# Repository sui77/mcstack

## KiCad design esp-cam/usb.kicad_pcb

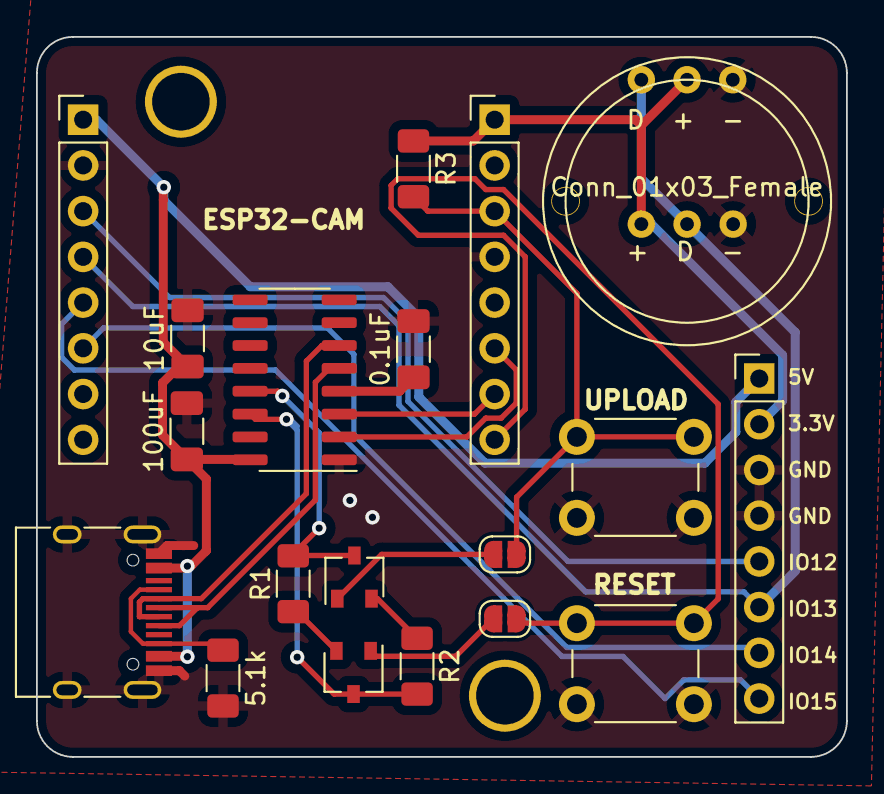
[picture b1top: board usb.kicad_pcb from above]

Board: 2 copper layers, 45.0 x 40.0 mm, 19 parts (0 on the bottom side), 21 nets.

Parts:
C1: 0.1uF; C_1206_3216Metric_Pad1.33x1.80mm_HandSolder
C3: 100uF; C_1206_3216Metric_Pad1.33x1.80mm_HandSolder
C4: 10uF; C_1206_3216Metric_Pad1.33x1.80mm_HandSolder
J1, J2, J5: Conn_01x08_Female; PinHeader_1x08_P2.54mm_Vertical
J3: USB_C_Receptacle; USB_C_Receptacle_HRO_TYPE-C-31-M-12
J4: Conn_01x03_Female; PIR
JP1, JP2: SolderJumper_2_Open; SolderJumper-2_P1.3mm_Open_RoundedPad1.0x1.5mm
Q1, Q2: BC547; SOT-23W
R1, R2, R3: R; R_1206_3216Metric_Pad1.30x1.75mm_HandSolder
R4: 5.1k; R_1206_3216Metric_Pad1.30x1.75mm_HandSolder
SW1, SW2: SW_Push; SW_PUSH_6mm
U1: CH340G; SOIC-16_3.9x9.9mm_P1.27mm

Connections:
3.3V: J2.1, J4.2, J5.2, R3.1
D+: J3.A6 (D+), J3.B6 (D+), U1.5 (UD+)
D-: J3.A7 (D-), J3.B7 (D-), U1.6 (UD-)
GND: C1.1, C3.1, C4.1, J1.2, J2.4, J3.A1 (GND), J3.A12 (GND), J3.B1 (GND), J3.B12 (GND), J3.S1 (SHIELD), J4.3, J5.3, J5.4, R4.1, SW1.2, SW2.2, U1.1 (GND)
GPIO0: J2.3, JP2.2 (B), R3.2, SW1.1
GPIO12: J1.3, J5.5
GPIO13: J1.4, J4.1, J5.6
GPIO14: J1.6, J5.7
GPIO15: J1.5, J5.8
unnamed: J3.A5 (CC1), J3.B5 (CC2), R4.2
unnamed: JP1.1 (A), Q1.1 (C)
unnamed: JP2.1 (A), Q2.1 (C)
unnamed: Q1.2 (B), R1.1
unnamed: Q1.3 (E), R2.2, U1.14 (~RTS)
unnamed: Q2.2 (B), R2.1
unnamed: Q2.3 (E), R1.2, U1.13 (~DTR)
unnamed: C1.2, U1.4 (V3)
RST: J2.8, JP1.2 (B), SW2.1
RX: J2.6, U1.2 (TXD)
TX: J2.7, U1.3 (RXD)
Vin: C3.2, C4.2, J1.1, J3.A4 (VBUS), J3.A9 (VBUS), J3.B4 (VBUS), J3.B9 (VBUS), J5.1, U1.16 (VCC)

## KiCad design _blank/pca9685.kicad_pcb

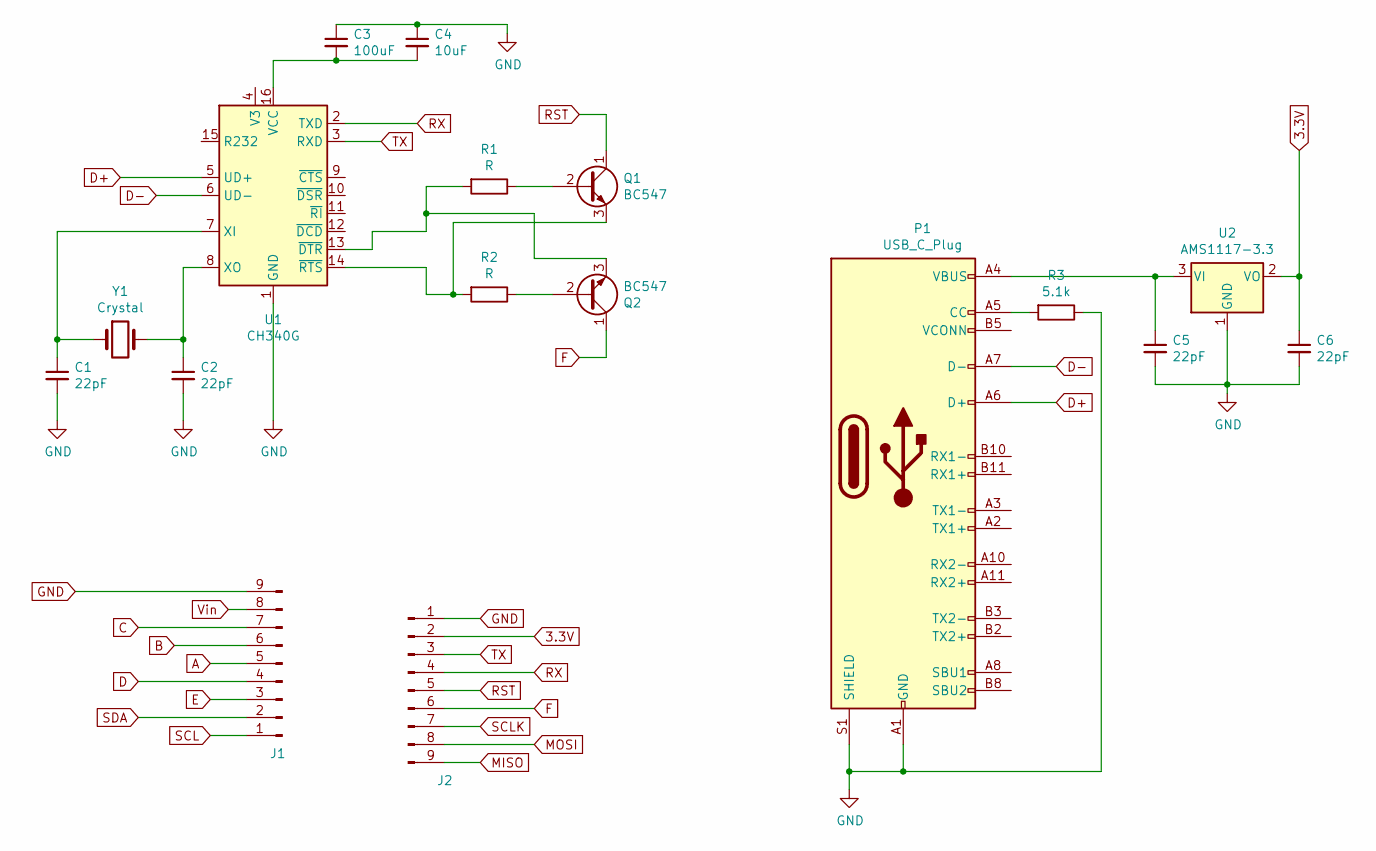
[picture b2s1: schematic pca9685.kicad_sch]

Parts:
C1, C2, C5, C6: 22pF; C_1206_3216Metric_Pad1.33x1.80mm_HandSolder
C3: 100uF; C_1206_3216Metric_Pad1.33x1.80mm_HandSolder
C4: 10uF; C_1206_3216Metric_Pad1.33x1.80mm_HandSolder
J1, J2: Conn_01x08_Male; PinHeader_1x09_P2.54mm_Vertical
P1: USB_C_Plug; USB_C_Receptacle_HRO_TYPE-C-31-M-12
Q1, Q2: BC547; SOT-23W
R1, R2: R; R_1206_3216Metric_Pad1.30x1.75mm_HandSolder
R3: 5.1k; R_1206_3216Metric_Pad1.30x1.75mm_HandSolder
U1: CH340G; SOIC-16_3.9x9.9mm_P1.27mm
U2: AMS1117-3.3; SOT-223-3_TabPin2
Y1: Crystal; 2pincrystal

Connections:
3.3V: C6.1, J2.2, U2.2 (VO)
A: J1.5
B: J1.6
C: J1.7
D: J1.4
D+: P1.A6 (D+), U1.5 (UD+)
D-: P1.A7 (D-), U1.6 (UD-)
E: J1.3
F: J2.6, Q2.1 (C)
GND: C1.2, C2.2, C3.1, C4.1, C5.2, C6.2, J1.9, J2.1, P1.A1 (GND), P1.A12 (GND), P1.B1 (GND), P1.B12 (GND), P1.S1 (SHIELD), R3.1, U1.1 (GND), U2.1 (GND)
MISO: J2.9
MOSI: J2.8
unnamed: C1.1, U1.7 (XI), Y1.1
unnamed: C2.1, U1.8 (XO), Y1.2
unnamed: C3.2, C4.2, U1.16 (VCC)
unnamed: C5.1, P1.A4 (VBUS), P1.A9 (VBUS), P1.B4 (VBUS), P1.B9 (VBUS), U2.3 (VI)
unnamed: P1.A5 (CC), R3.2
unnamed: Q1.2 (B), R1.1
unnamed: Q1.3 (E), R2.2, U1.14 (~RTS)
unnamed: Q2.2 (B), R2.1
unnamed: Q2.3 (E), R1.2, U1.13 (~DTR)
RST: J2.5, Q1.1 (C)
RX: J2.4, U1.2 (TXD)
SCL: J1.1
SCLK: J2.7
SDA: J1.2
TX: J2.3, U1.3 (RXD)
Vin: J1.8

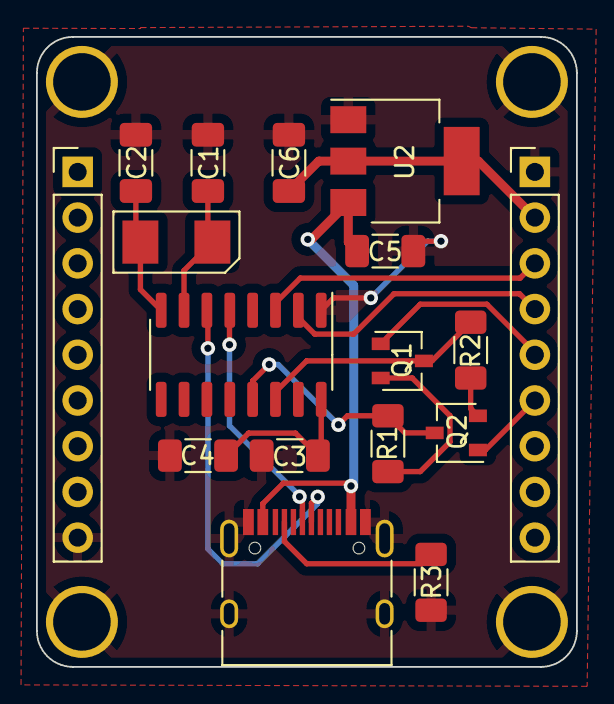
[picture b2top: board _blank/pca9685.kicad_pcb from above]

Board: 2 copper layers, 30.0 x 35.0 mm, 17 parts (0 on the bottom side), 17 nets.

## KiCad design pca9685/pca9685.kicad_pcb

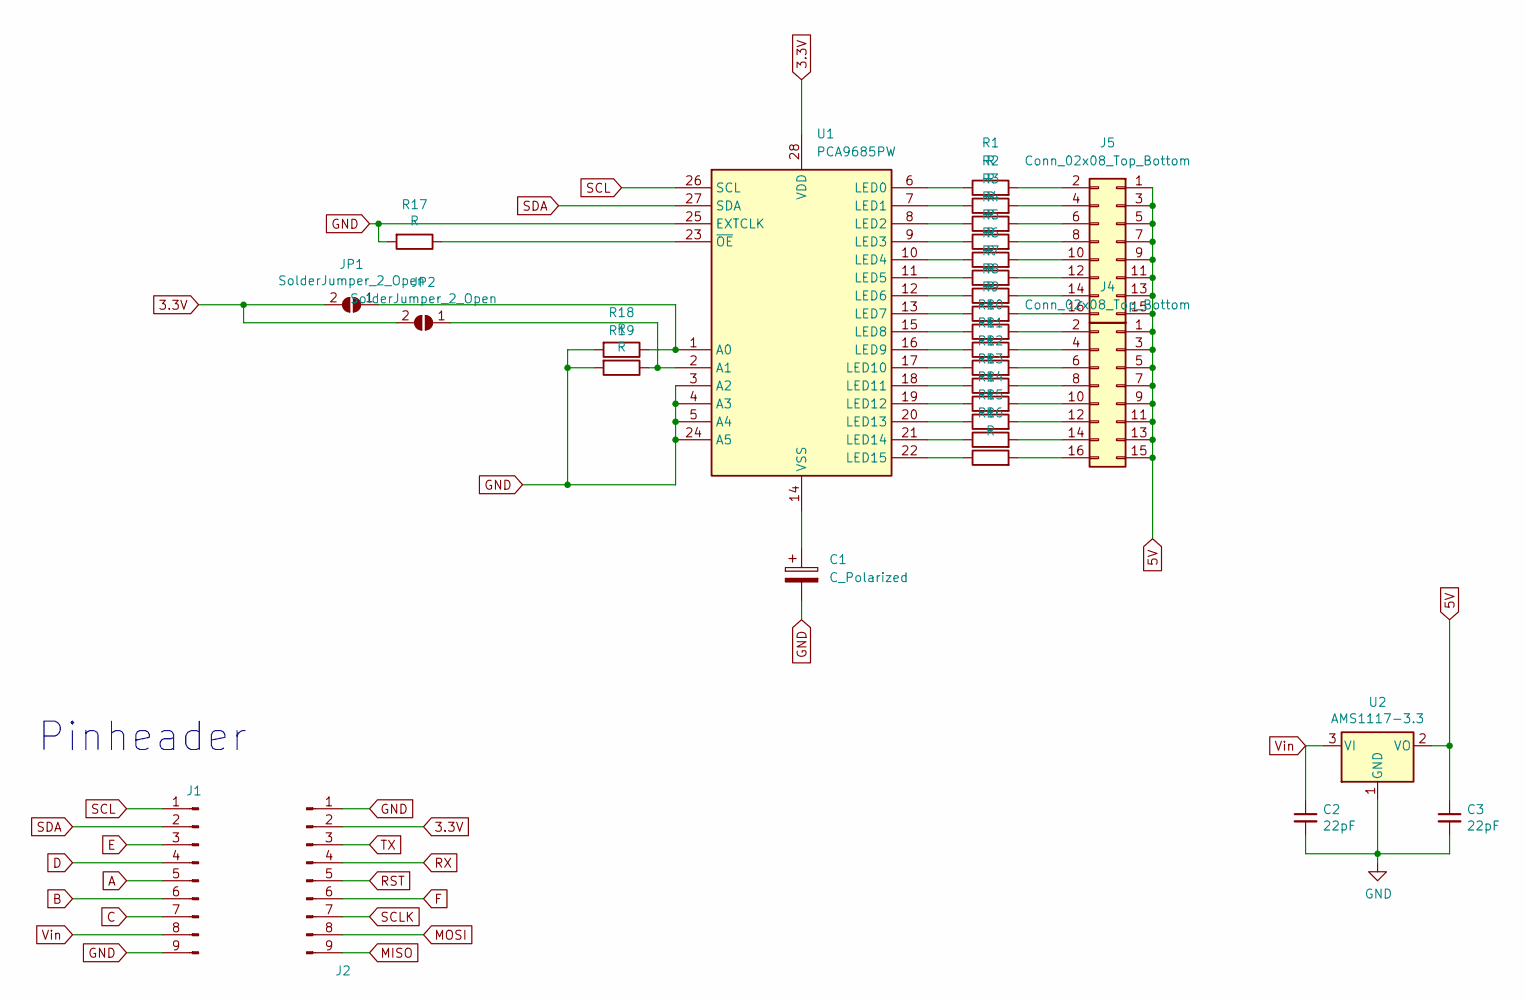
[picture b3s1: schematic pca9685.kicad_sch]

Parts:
C1: C_Polarized; CP_Radial_D8.0mm_P3.80mm
C2, C3: 22pF; C_1206_3216Metric_Pad1.33x1.80mm_HandSolder
J1, J2: Conn_01x08_Male; PinHeader_1x09_P2.54mm_Vertical
J4, J5: Conn_02x08_Top_Bottom; PinHeader_2x08_P2.54mm_Horizontal
JP1, JP2: SolderJumper_2_Open; SolderJumper-2_P1.3mm_Open_RoundedPad1.0x1.5mm
R1, R2, R3, R4, R5, R6, R7, R8, R9, R10, R11, R12, R13, R14, R15, R16, R17, R18, R19: R; R_1206_3216Metric_Pad1.30x1.75mm_HandSolder
U1: PCA9685PW; TSSOP-28_4.4x9.7mm_P0.65mm
U2: AMS1117-3.3; SOT-223-3_TabPin2

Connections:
3.3V: J2.2, JP1.2 (B), JP2.2 (B), U1.28 (VDD); also elsewhere on the board
5V: C3.1, J4.1, J4.3, J4.5, J4.7, J4.9, J4.11, J4.13, J4.15, J5.1, J5.3, J5.5, J5.7, J5.9, J5.11, J5.13, J5.15, U2.2 (VO)
A: J1.5
B: J1.6
C: J1.7
D: J1.4
E: J1.3
F: J2.6
GND: C1.2, C2.2, C3.2, J1.9, J2.1, R17.2, R18.2, R19.2, U1.3 (A2), U1.4 (A3), U1.5 (A4), U1.24 (A5), U1.25 (EXTCLK), U2.1 (GND)
MISO: J2.9
MOSI: J2.8
unnamed: J4.6, R11.2
unnamed: R1.1, U1.6 (LED0)
unnamed: J5.2, R1.2
unnamed: R2.1, U1.7 (LED1)
unnamed: J5.4, R2.2
unnamed: R3.1, U1.8 (LED2)
unnamed: J5.6, R3.2
unnamed: R4.1, U1.9 (LED3)
unnamed: J5.8, R4.2
unnamed: R5.1, U1.10 (LED4)
unnamed: J5.10, R5.2
unnamed: R6.1, U1.11 (LED5)
unnamed: J5.12, R6.2
unnamed: R7.1, U1.12 (LED6)
unnamed: J5.14, R7.2
unnamed: R8.1, U1.13 (LED7)
unnamed: J5.16, R8.2
unnamed: R9.1, U1.15 (LED8)
unnamed: J4.2, R9.2
unnamed: R10.1, U1.16 (LED9)
unnamed: J4.4, R10.2
unnamed: R11.1, U1.17 (LED10)
unnamed: R12.1, U1.18 (LED11)
unnamed: J4.8, R12.2
unnamed: R13.1, U1.19 (LED12)
unnamed: J4.10, R13.2
unnamed: R14.1, U1.20 (LED13)
unnamed: J4.12, R14.2
unnamed: R15.1, U1.21 (LED14)
unnamed: J4.14, R15.2
unnamed: R16.1, U1.22 (LED15)
unnamed: J4.16, R16.2
unnamed 43: JP1.1 (A), R18.1, U1.1 (A0); also elsewhere on the board
unnamed 44: JP2.1 (A), R19.1, U1.2 (A1); also elsewhere on the board
unnamed: C1.1, U1.14 (VSS)
unnamed: R17.1, U1.23 (~OE)
RST: J2.5
RX: J2.4
SCL: J1.1, U1.26 (SCL)
SCLK: J2.7
SDA: J1.2, U1.27 (SDA)
TX: J2.3
Vin: C2.1, J1.8, U2.3 (VI)

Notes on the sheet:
Pinheader

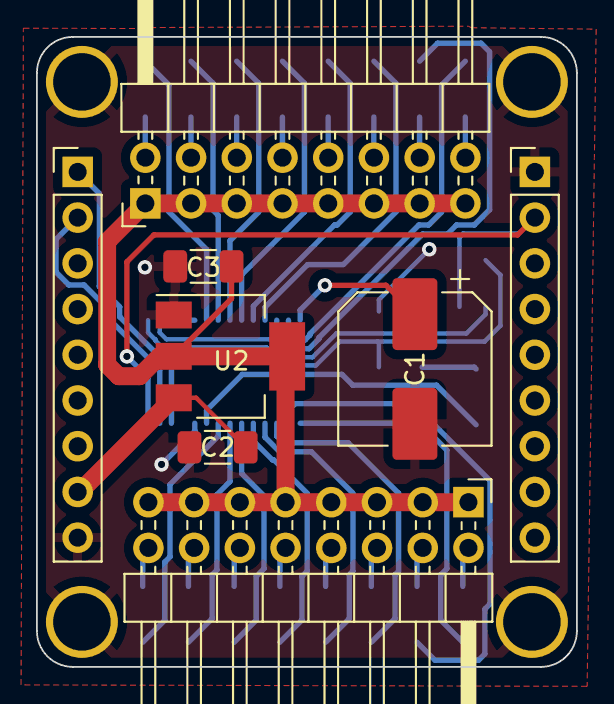
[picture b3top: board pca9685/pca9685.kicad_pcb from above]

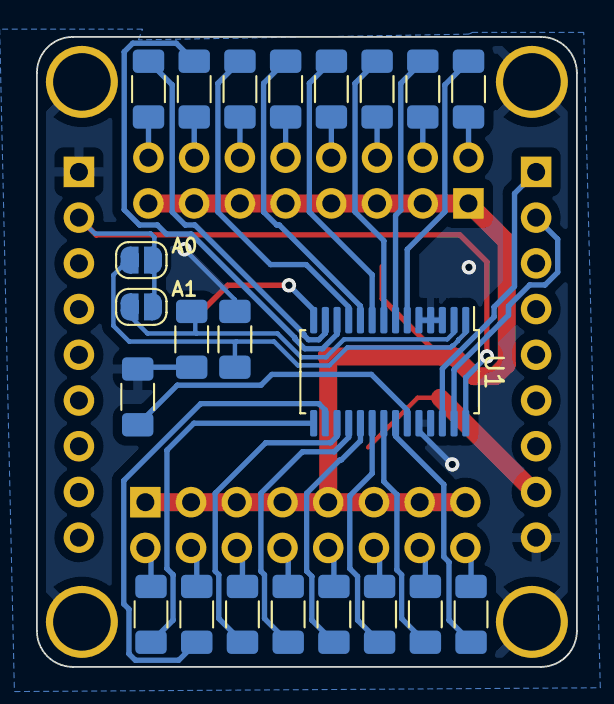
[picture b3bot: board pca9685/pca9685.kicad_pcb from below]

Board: 2 copper layers, 30.0 x 35.0 mm, 30 parts (22 on the bottom side), 42 nets.

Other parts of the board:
A0, A1: SolderJumper_2_Open; SolderJumper-2_P1.3mm_Open_RoundedPad1.0x1.5mm

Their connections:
3.3V: A0.2 (B), A1.2 (B); also elsewhere on the board
unnamed 43: A0.1 (A); also elsewhere on the board
unnamed 44: A1.1 (A); also elsewhere on the board

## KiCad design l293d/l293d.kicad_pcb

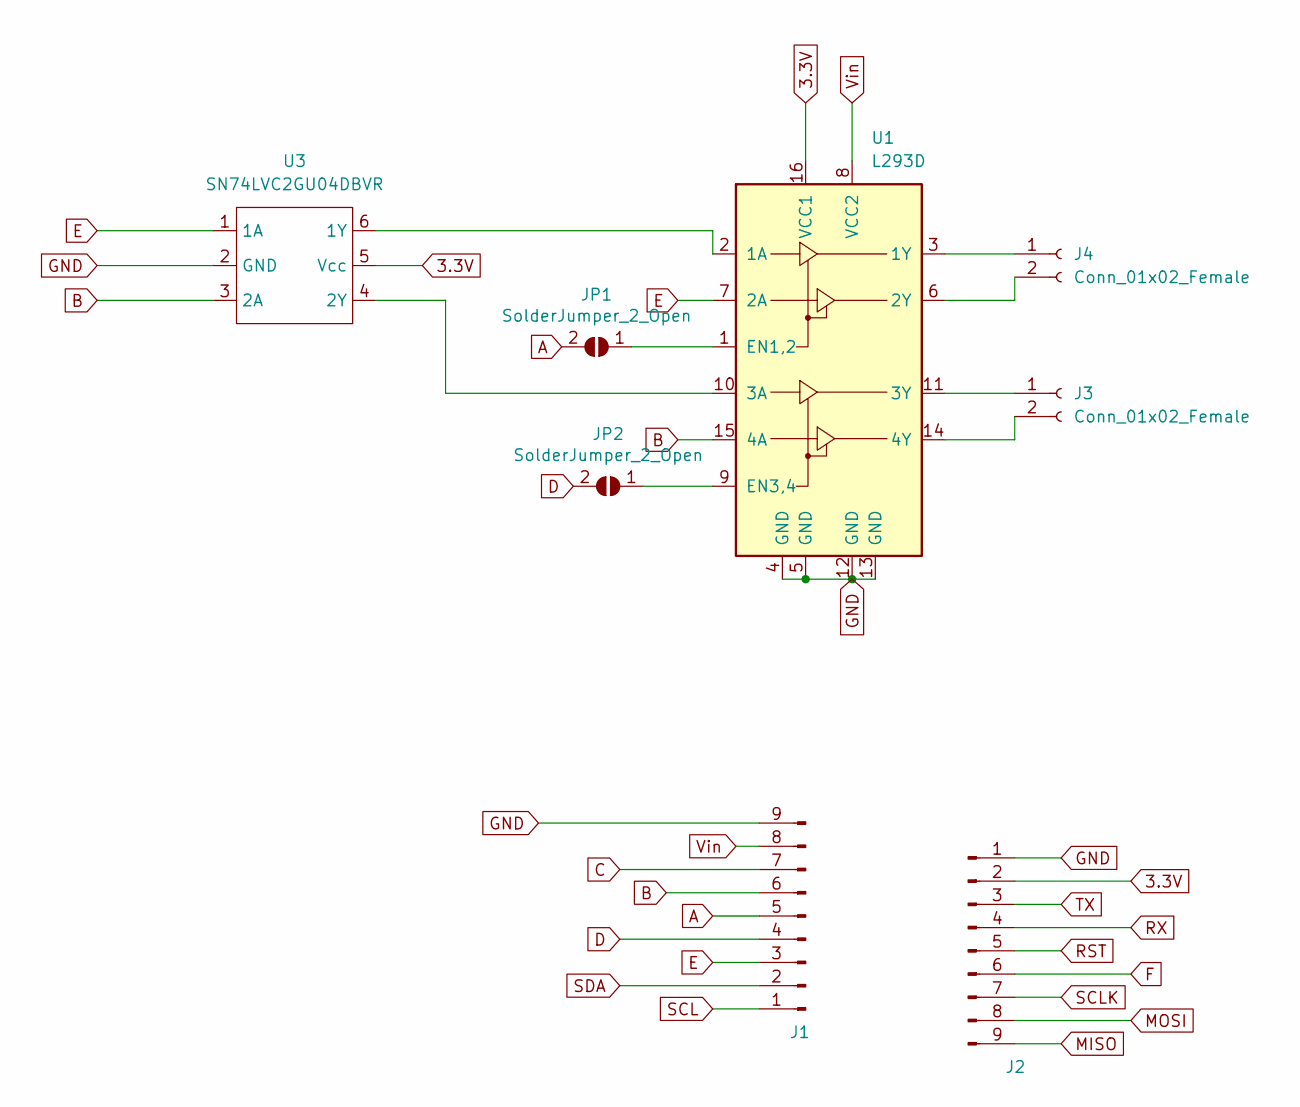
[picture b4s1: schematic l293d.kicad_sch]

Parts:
J1, J2: Conn_01x08_Male; PinHeader_1x09_P2.54mm_Vertical
J3, J4: Conn_01x02_Female; JST_XH_B2B-XH-A_1x02_P2.50mm_Vertical
JP1, JP2: SolderJumper_2_Open; SolderJumper-2_P1.3mm_Open_RoundedPad1.0x1.5mm
U1: L293D; DIP-16_W7.62mm
U3: SN74LVC2GU04DBVR; SOT-23-6_Handsoldering

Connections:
3.3V: J2.2, U1.16 (VCC1), U3.5 (Vcc)
A: J1.5, JP1.2 (B)
B: J1.6, U1.15 (4A), U3.3 (2A)
C: J1.7
D: J1.4, JP2.2 (B)
E: J1.3, U1.7 (2A), U3.1 (1A)
F: J2.6
GND: J1.9, J2.1, U1.4 (GND), U1.5 (GND), U1.12 (GND), U1.13 (GND), U3.2 (GND)
MISO: J2.9
MOSI: J2.8
unnamed: J3.1, U1.11 (3Y)
unnamed: J3.2, U1.14 (4Y)
unnamed: J4.1, U1.3 (1Y)
unnamed: J4.2, U1.6 (2Y)
unnamed: JP1.1 (A), U1.1 (EN1,2)
unnamed: JP2.1 (A), U1.9 (EN3,4)
unnamed: U1.2 (1A), U3.6 (1Y)
unnamed: U1.10 (3A), U3.4 (2Y)
RST: J2.5
RX: J2.4
SCL: J1.1
SCLK: J2.7
SDA: J1.2
TX: J2.3
Vin: J1.8, U1.8 (VCC2)

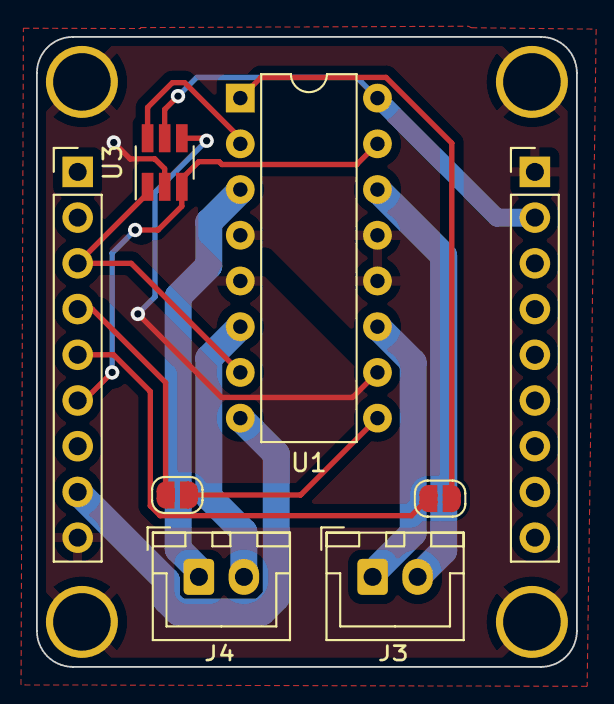
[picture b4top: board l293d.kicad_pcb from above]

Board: 2 copper layers, 30.0 x 35.0 mm, 8 parts (0 on the bottom side), 15 nets.

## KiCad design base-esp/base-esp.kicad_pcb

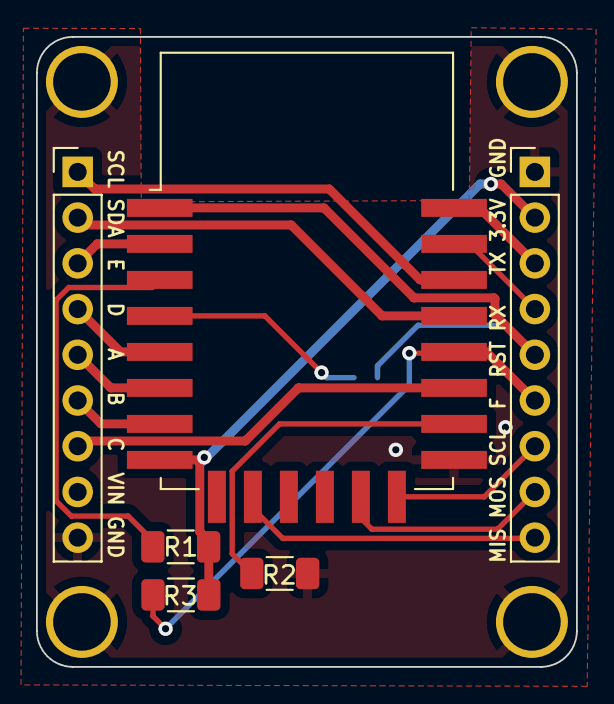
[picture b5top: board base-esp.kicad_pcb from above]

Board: 2 copper layers, 30.0 x 35.0 mm, 7 parts (1 on the bottom side), 19 nets.

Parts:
J1, J2: Conn_01x08_Male; PinHeader_1x09_P2.54mm_Vertical
R1, R2, R3: 12k; R_1206_3216Metric_Pad1.30x1.75mm_HandSolder
U1: ESP-12E
WAKE - RST: SolderJumper_2_Open; SolderJumper-2_P1.3mm_Open_RoundedPad1.0x1.5mm

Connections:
3.3V: J2.2, R1.2, R3.2, U1.8 (VCC)
A: J1.5, U1.6 (GPIO12)
B: J1.6, U1.7 (GPIO13)
C: J1.7, U1.17 (GPIO2)
D: J1.4, U1.5 (GPIO14)
E: J1.3, U1.2 (ADC)
F: J2.6, R3.1, U1.18 (GPIO0)
GND: J1.9, J2.1, R2.1, U1.15 (GND)
MISO: J2.9, U1.10 (MISO)
MOSI: J2.8, U1.13 (MOSI)
unnamed: U1.4 (GPIO16), WAKE - RST.2 (B)
unnamed: R1.1, U1.3 (EN)
unnamed: R2.2, U1.16 (GPIO15)
RST: J2.5, U1.1 (~RST), WAKE - RST.1 (A)
RX: J2.4, U1.21 (GPIO3/RXD)
SCL: J1.1, U1.20 (GPIO5)
SCLK: J2.7, U1.14 (SCLK)
SDA: J1.2, U1.19 (GPIO4)
TX: J2.3, U1.22 (GPIO1/TXD)

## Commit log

2022-03-21 initial push
